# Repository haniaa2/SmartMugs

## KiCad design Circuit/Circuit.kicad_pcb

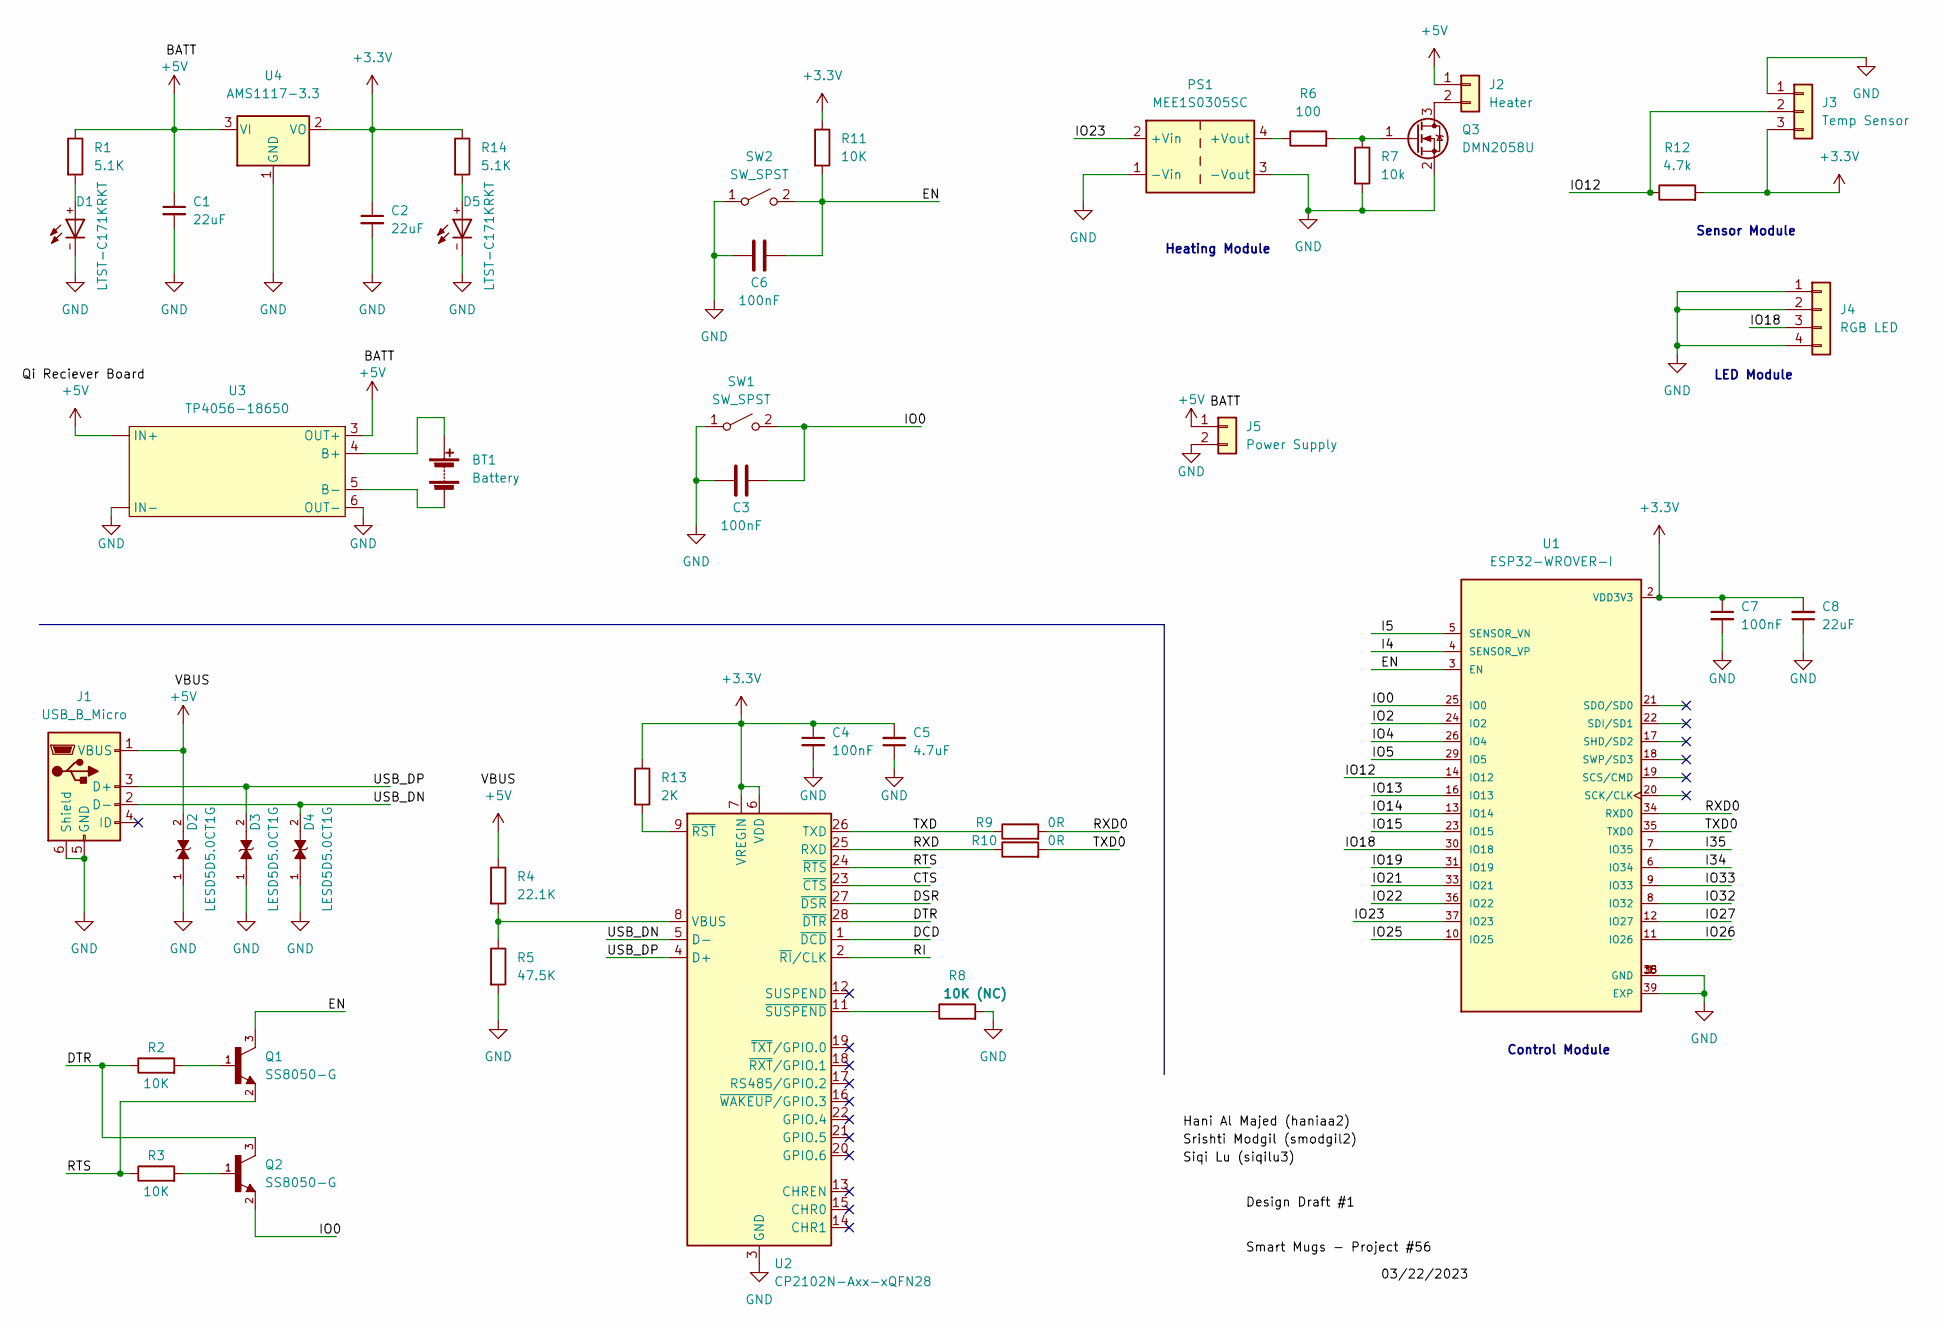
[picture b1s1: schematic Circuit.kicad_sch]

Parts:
BT1: Battery
C1, C2, C8: 22uF; C_0805_2012Metric_Pad1.18x1.45mm_HandSolder
C3, C4, C6, C7: 100nF; C_0805_2012Metric_Pad1.18x1.45mm_HandSolder
C5: 4.7uF; C_0805_2012Metric_Pad1.18x1.45mm_HandSolder
D1, D5: LTST-C171KRKT; DIOC200X125X110
D2, D3, D4: LESD5D5.0CT1G; TVS_LESD5D5.0CT1G; PARTREV O
J1: USB_B_Micro; USB_Micro-B_Molex-105017-0001
J2: Heater; Molex_KK-254_AE-6410-02A_1x02_P2.54mm_Vertical
J3: Temp Sensor; Molex_KK-254_AE-6410-03A_1x03_P2.54mm_Vertical
J4: RGB LED; Molex_KK-254_AE-6410-04A_1x04_P2.54mm_Vertical
J5: Power Supply; Molex_KK-254_AE-6410-02A_1x02_P2.54mm_Vertical
PS1: MEE1S0305SC; Converter_DCDC_Murata_MEE1SxxxxSC_THT
Q1, Q2: SS8050-G; TRANS_SS8050-G; PARTREV A
Q3: DMN2058U; SOT-23
R1, R14: 5.1K; R_0805_2012Metric_Pad1.20x1.40mm_HandSolder
R2, R3, R11: 10K; R_0805_2012Metric_Pad1.20x1.40mm_HandSolder
R4: 22.1K; R_0805_2012Metric_Pad1.20x1.40mm_HandSolder
R5: 47.5K; R_0805_2012Metric_Pad1.20x1.40mm_HandSolder
R6: 100; R_0805_2012Metric_Pad1.20x1.40mm_HandSolder
R7: 10k; R_0805_2012Metric_Pad1.20x1.40mm_HandSolder
R8: 10K (NC); R_0805_2012Metric_Pad1.20x1.40mm_HandSolder
R9, R10: 0R; R_0805_2012Metric_Pad1.20x1.40mm_HandSolder
R12: 4.7k; R_0805_2012Metric_Pad1.20x1.40mm_HandSolder
R13: 2K; R_0805_2012Metric_Pad1.20x1.40mm_HandSolder
SW1, SW2: SW_SPST; SW_Push_1P1T_NO_CK_KSC6xxJ
U1: ESP32-WROVER-I; XCVR_ESP32-WROVER-I; DIGI-KEY_PART_NUMBER 1904-1008-1-ND
U2: CP2102N-Axx-xQFN28; QFN-28-1EP_5x5mm_P0.5mm_EP3.35x3.35mm
U3: TP4056-18650
U4: AMS1117-3.3; SOT-223-3_TabPin2

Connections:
+3.3V: C2.1, C4.1, C5.2, C7.1, C8.2, J3.3, R11.1, R12.2, R13.1, R14.1, U1.2 (VDD3V3), U2.6 (VDD), U2.7 (VREGIN), U4.2 (VO)
+5V: C1.1, D2.2, J1.1 (VBUS), J2.1, J5.1, R1.1, R4.1, U3. (IN+), U3.3 (OUT+), U4.3 (VI)
/CTS: U2.23 (~CTS)
/DCD: U2.1 (~DCD)
/DSR: U2.27 (~DSR)
/DTR: Q2.3, R2.1, U2.28 (~DTR)
/EN: C6.2, Q1.3, R11.2, SW2.2 (B), U1.3 (EN)
/I4: U1.4 (SENSOR_VP)
/I5: U1.5 (SENSOR_VN)
/I34: U1.6 (IO34)
/I35: U1.7 (IO35)
/IO0: C3.2, Q2.2, SW1.2 (B), U1.25 (IO0)
/IO2: U1.24 (IO2)
/IO4: U1.26 (IO4)
/IO5: U1.29 (IO5)
/IO12: J3.2, R12.1, U1.14 (IO12)
/IO13: U1.16 (IO13)
/IO14: U1.13 (IO14)
/IO15: U1.23 (IO15)
/IO18: J4.3, U1.30 (IO18)
/IO19: U1.31 (IO19)
/IO21: U1.33 (IO21)
/IO22: U1.36 (IO22)
/IO23: PS1.2 (+Vin), U1.37 (IO23)
/IO25: U1.10 (IO25)
/IO26: U1.11 (IO26)
/IO27: U1.12 (IO27)
/IO32: U1.8 (IO32)
/IO33: U1.9 (IO33)
/RI: U2.2 (~RI/CLK)
/RTS: Q1.2, R3.1, U2.24 (~RTS)
/RXD: R10.1, U2.25 (RXD)
/RXD0: R9.2, U1.34 (RXD0)
/TXD: R9.1, U2.26 (TXD)
/TXD0: R10.2, U1.35 (TXD0)
/USB_DN: D4.2, J1.2 (D-), U2.5 (D-)
/USB_DP: D3.2, J1.3 (D+), U2.4 (D+)
GND: C1.2, C2.2, C3.1, C4.2, C5.1, C6.1, C7.2, C8.1, D1.-, D2.1, D3.1, D4.1, D5.-, J1.5 (GND), J1.6 (Shield), J3.1, J4.1, J4.2, J4.4, J5.2, PS1.1 (-Vin), PS1.3 (-Vout), Q3.2 (S), R5.2, R7.2, R8.2, SW1.1 (A), SW2.1 (A), U1.1 (GND), U1.15 (GND), U1.38 (GND), U1.39 (EXP), U2.3 (GND), U2.29 (GND), U3. (IN+), U3.6 (OUT-), U4.1 (GND)
unnamed: BT1.1 (+), U3.4 (B+)
unnamed: BT1.2 (-), U3.5 (B-)
unnamed: D5.+, R14.2
unnamed: J2.2, Q3.3 (D)
unnamed: PS1.4 (+Vout), R6.1
unnamed: Q1.1, R2.2
unnamed: Q2.1, R3.2
unnamed: Q3.1 (G), R6.2, R7.1
unnamed: D1.+, R1.2
unnamed: R4.2, R5.1, U2.8 (VBUS)
unnamed: R8.1, U2.11 (~SUSPEND)
unnamed: R13.2, U2.9 (~RST)

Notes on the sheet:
Control Module
Sensor Module
Heating Module
LED Module

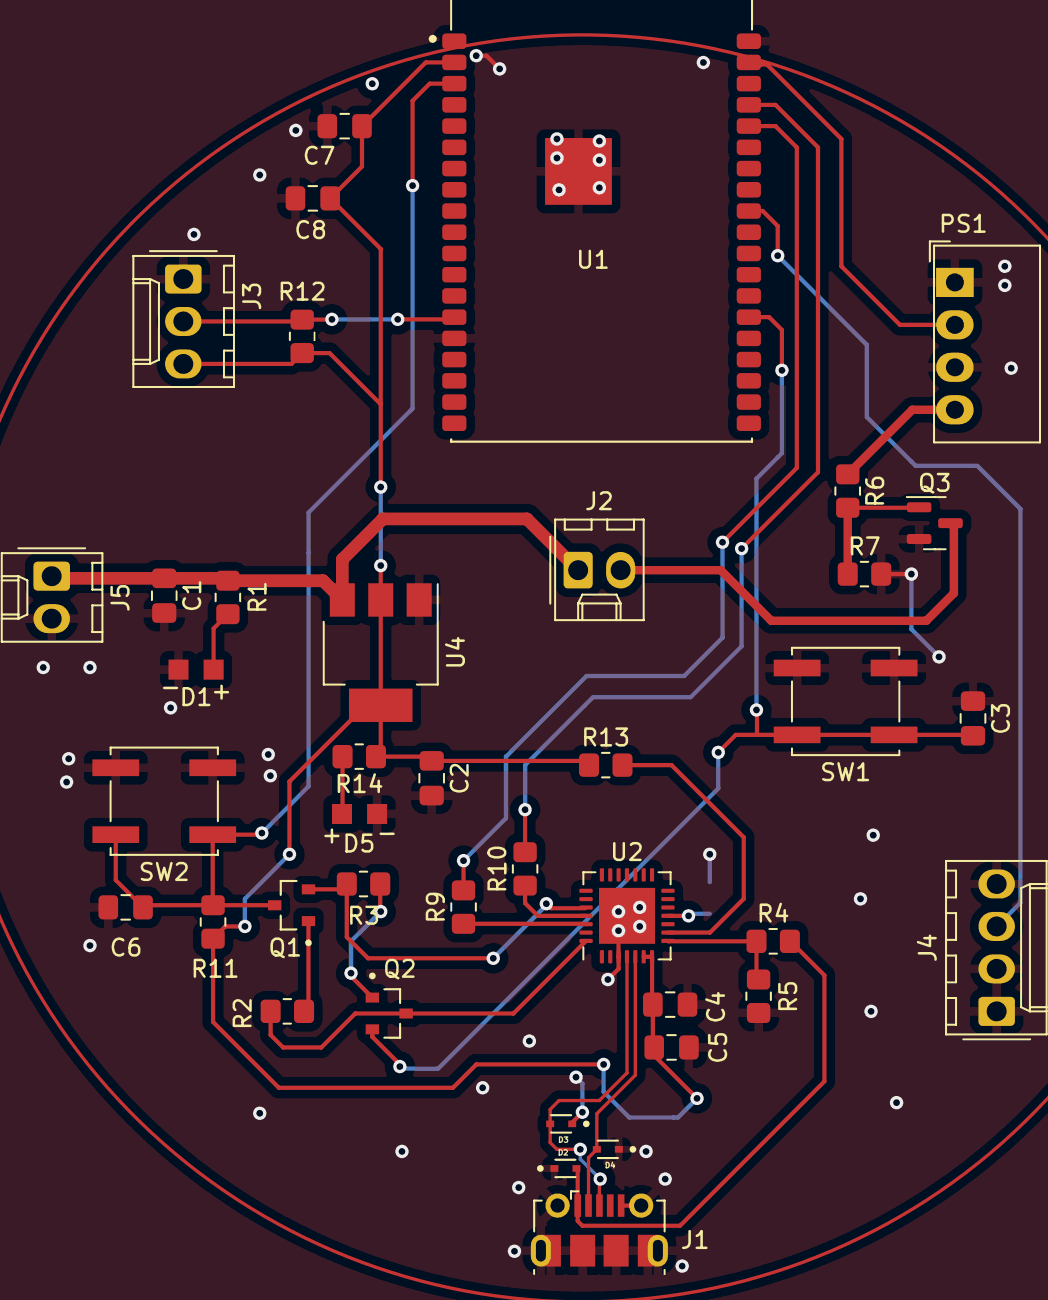
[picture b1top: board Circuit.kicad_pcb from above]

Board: 2 copper layers, 41 parts (1 on the bottom side), 26 nets.

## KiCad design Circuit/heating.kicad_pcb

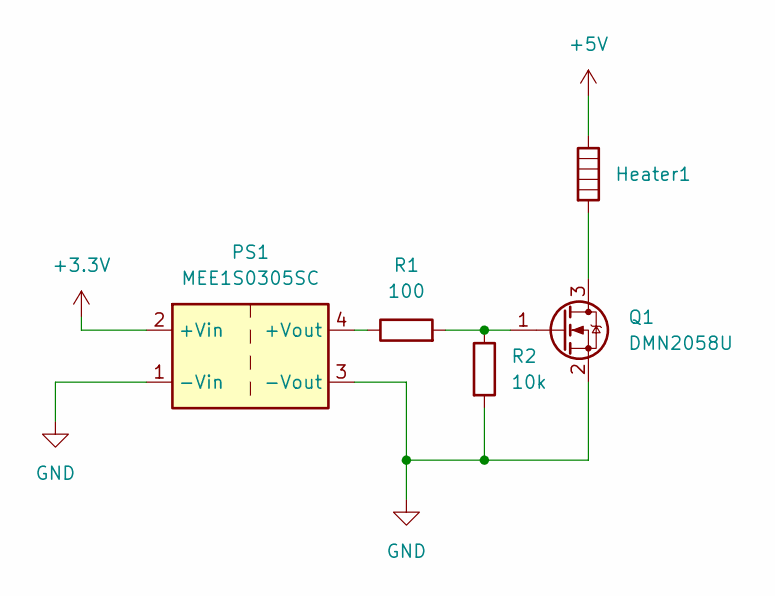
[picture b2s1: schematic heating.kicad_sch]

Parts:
Heater1: Heater; R_0805_2012Metric_Pad1.20x1.40mm_HandSolder
PS1: MEE1S0305SC; Converter_DCDC_Murata_MEE1SxxxxSC_THT
Q1: DMN2058U; SOT-23
R1: 100; R_0805_2012Metric_Pad1.20x1.40mm_HandSolder
R2: 10k; R_0805_2012Metric_Pad1.20x1.40mm_HandSolder

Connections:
+3.3V: PS1.2 (+Vin)
+5V: Heater1.1
GND: PS1.1 (-Vin), PS1.3 (-Vout), Q1.2 (S), R2.2
unnamed: Heater1.2, Q1.3 (D)
unnamed: PS1.4 (+Vout), R1.1
unnamed: Q1.1 (G), R1.2, R2.1

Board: 2 copper layers, 5 parts (0 on the bottom side), 4 nets, no tracks yet.

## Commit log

2023-02-21 change proposal.docx -> .md
2023-02-21 /.Notebooks
2023-02-21 Create siqilu3
2023-02-21 update notebook
2023-03-08 add sch
2023-03-27 PUA0305S1A
    DC/DC CONVERTER 5V 1W
2023-03-29 Update Circuit.sch file
2023-03-31 latest
2023-04-01 updated sch
2023-04-02 Update PCB
2023-04-12 update log
2023-04-18 Add files via upload
    add heating part design
2023-04-23 Add Serverless FB
2023-04-23 Update notebooks
2023-04-23 Add files via upload
    testing log of the heating subsystem
2023-04-24 Hani: update mcu=8266 for rtdb
2023-04-24 Add files via upload
    heating and sensing
2023-04-29 Updated Heating and Sensor Subsystem code
2023-04-29 esp32
    hi
2023-04-29 Create esp32-test
2023-04-29 Create esp32_test2
2023-04-29 Almost completed
    heating element circuit yet to be done; wifi controlled circuit on and off of the LED works using esp32; temperature should be detected correctly but not verified yet; the LED indicate if the heater 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
2023-05-02 Completed Code
2023-05-02 Create datasheets
2023-05-02 datasheets
2023-05-02 updated completed code
2023-05-02 add test files for heating system
2023-05-02 esp32 tutorial
2023-05-02 Design Document
2023-05-02 Add Design Document
2023-05-02 visual aid
2023-05-03 Create updated_website
2023-05-05 final block diagram fig
